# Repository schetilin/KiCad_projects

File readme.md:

Проекты KiCad 5

Так как я сварщик не настоящий, то проекты мааааленькие, тренировочные :)

1. Пищалка (Buzzer) на 2 транзисторах
2. Имитатор пения птиц :)

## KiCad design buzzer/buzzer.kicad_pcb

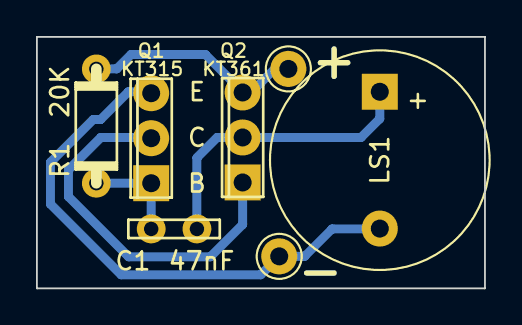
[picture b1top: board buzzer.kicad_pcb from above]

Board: 2 copper layers, 24.9 x 14.0 mm, 7 parts (0 on the bottom side), 5 nets.

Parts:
+: +; Pin_D1.0mm_L10.0mm
-: -; Pin_D1.0mm_L10.0mm
C1: 47nF; ceramic_5
LS1: Earphone; Buzzer_12x9.5RM7.6
Q1: KT315; kt315
Q2: KT361; kt315
R1: 20K; MLT_0.125_10

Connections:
unnamed: C1.1, Q1.B, R1.1
unnamed: C1.2, LS1.1, Q2.C
unnamed: +.1, Q2.E, R1.2
unnamed: -.1, LS1.2, Q1.E
unnamed: Q1.C, Q2.B

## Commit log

2020-04-22 initial project version
2020-04-22 add readme
2020-04-22 Правка readme
2020-04-22 clear bak and temp files
2020-04-23 edit readme
